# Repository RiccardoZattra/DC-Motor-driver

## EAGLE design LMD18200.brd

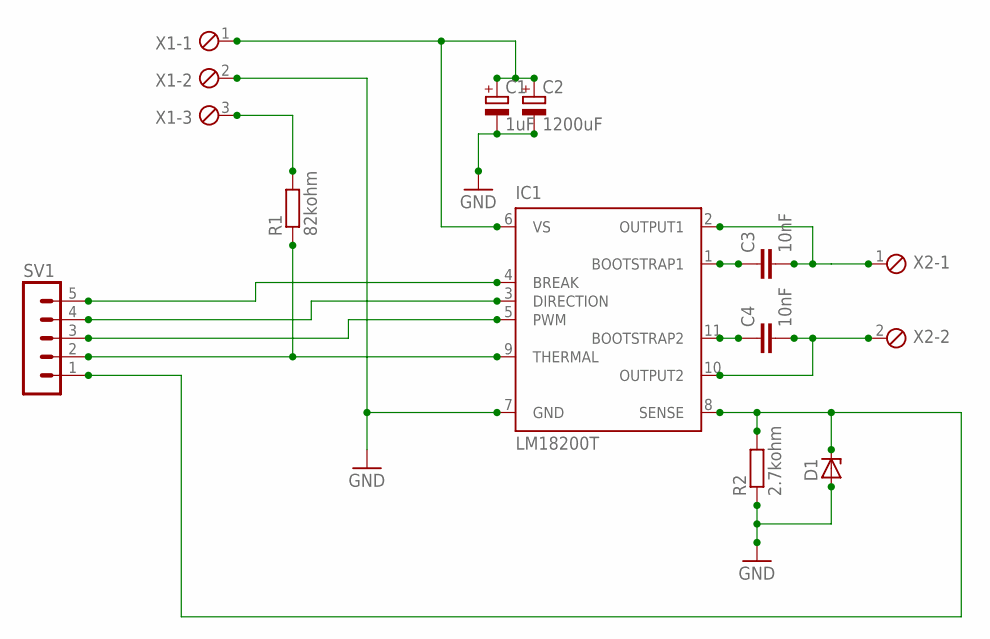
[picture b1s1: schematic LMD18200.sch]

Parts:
C1: 1uF; E2,5-6E
C2: 1200uF; E5-13
C3, C4: 10nF; C025-024X044
D1: ZENER-DIODEZD-5; ZDIO-5
IC1: LM18200T; TO-220-11
R1: 82kohm; 0204/5
R2: 2.7kohm; 0204/5
SV1: MA05-1
X1: MPT3; 3POL254
X2: MPT2; 2POL254

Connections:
GND: C1.-, C2.-, D1.A, IC1.7 (GND), R2.1, X1.2
unnamed: IC1.4 (BREAK), SV1.5
unnamed: IC1.3 (DIRECTION), SV1.4
unnamed: IC1.5 (PWM), SV1.3
unnamed: C3.1, IC1.1 (BOOTSTRAP1)
unnamed: C1.+, C2.+, IC1.6 (VS), X1.1
unnamed: IC1.9 (THERMAL), R1.1, SV1.2
unnamed: R1.2, X1.3
unnamed: C3.2, IC1.2 (OUTPUT1), X2.1
unnamed: C4.2, IC1.10 (OUTPUT2), X2.2
unnamed: D1.C, IC1.8 (SENSE), R2.2, SV1.1
unnamed: C4.1, IC1.11 (BOOTSTRAP2)

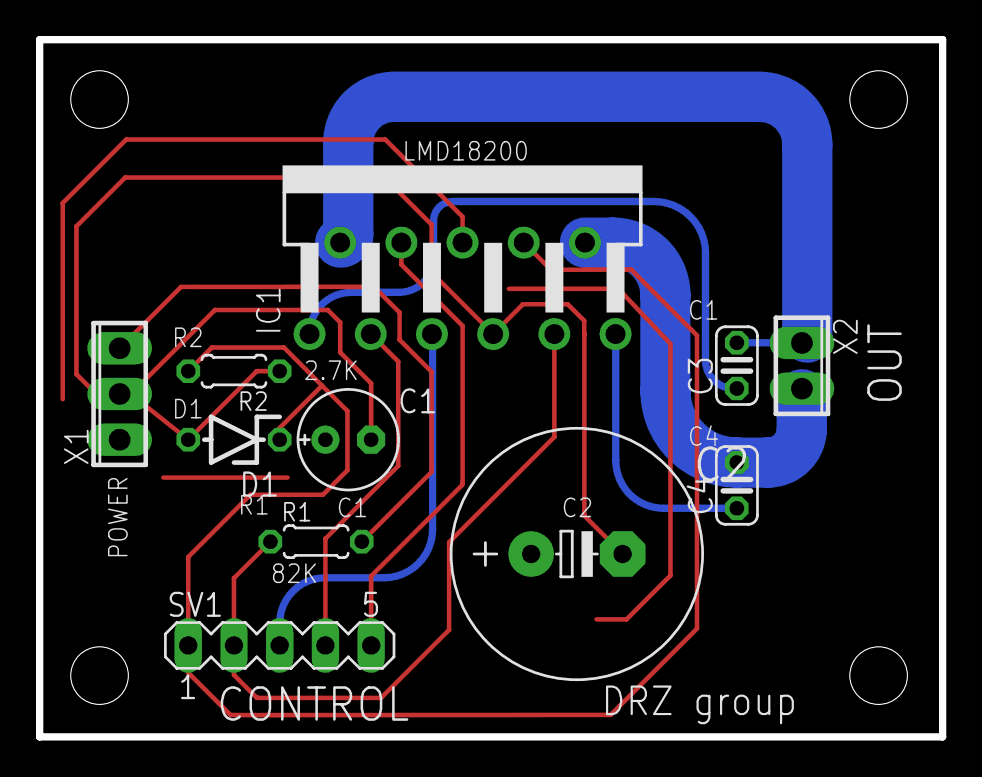
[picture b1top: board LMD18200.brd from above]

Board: 2 copper layers, 50.2 x 38.7 mm, 11 parts (0 on the bottom side), 12 nets.

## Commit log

2025-04-03 New files added
